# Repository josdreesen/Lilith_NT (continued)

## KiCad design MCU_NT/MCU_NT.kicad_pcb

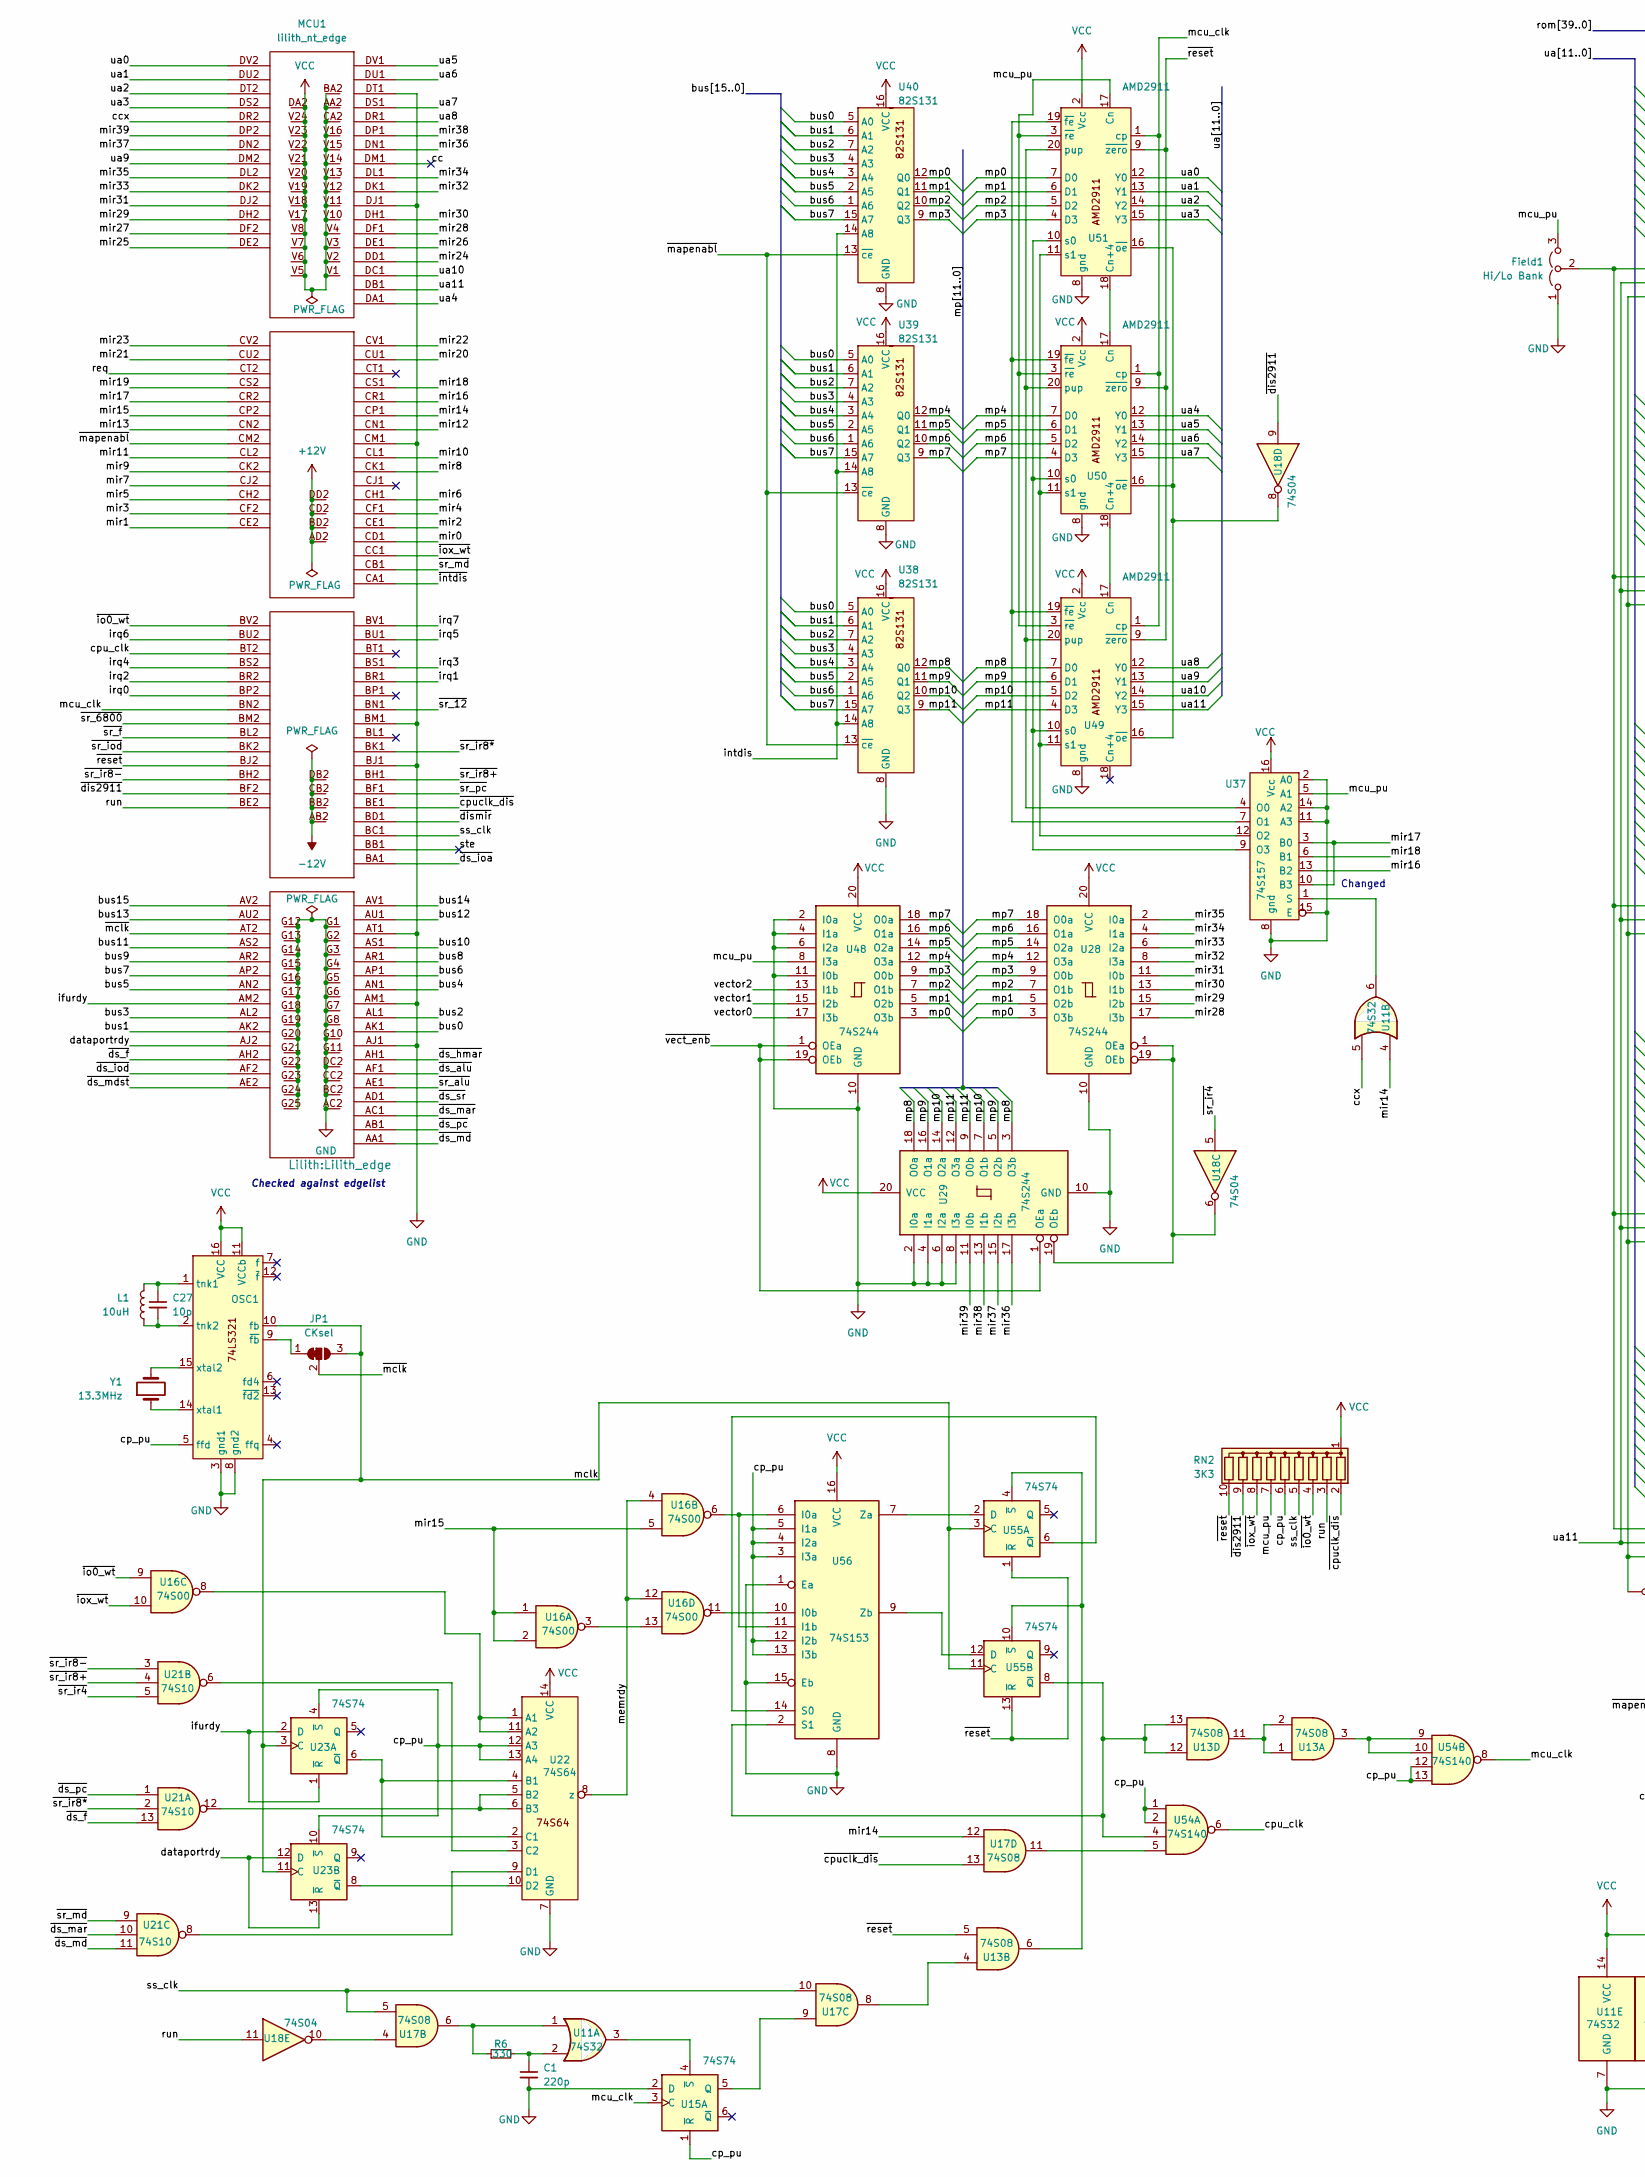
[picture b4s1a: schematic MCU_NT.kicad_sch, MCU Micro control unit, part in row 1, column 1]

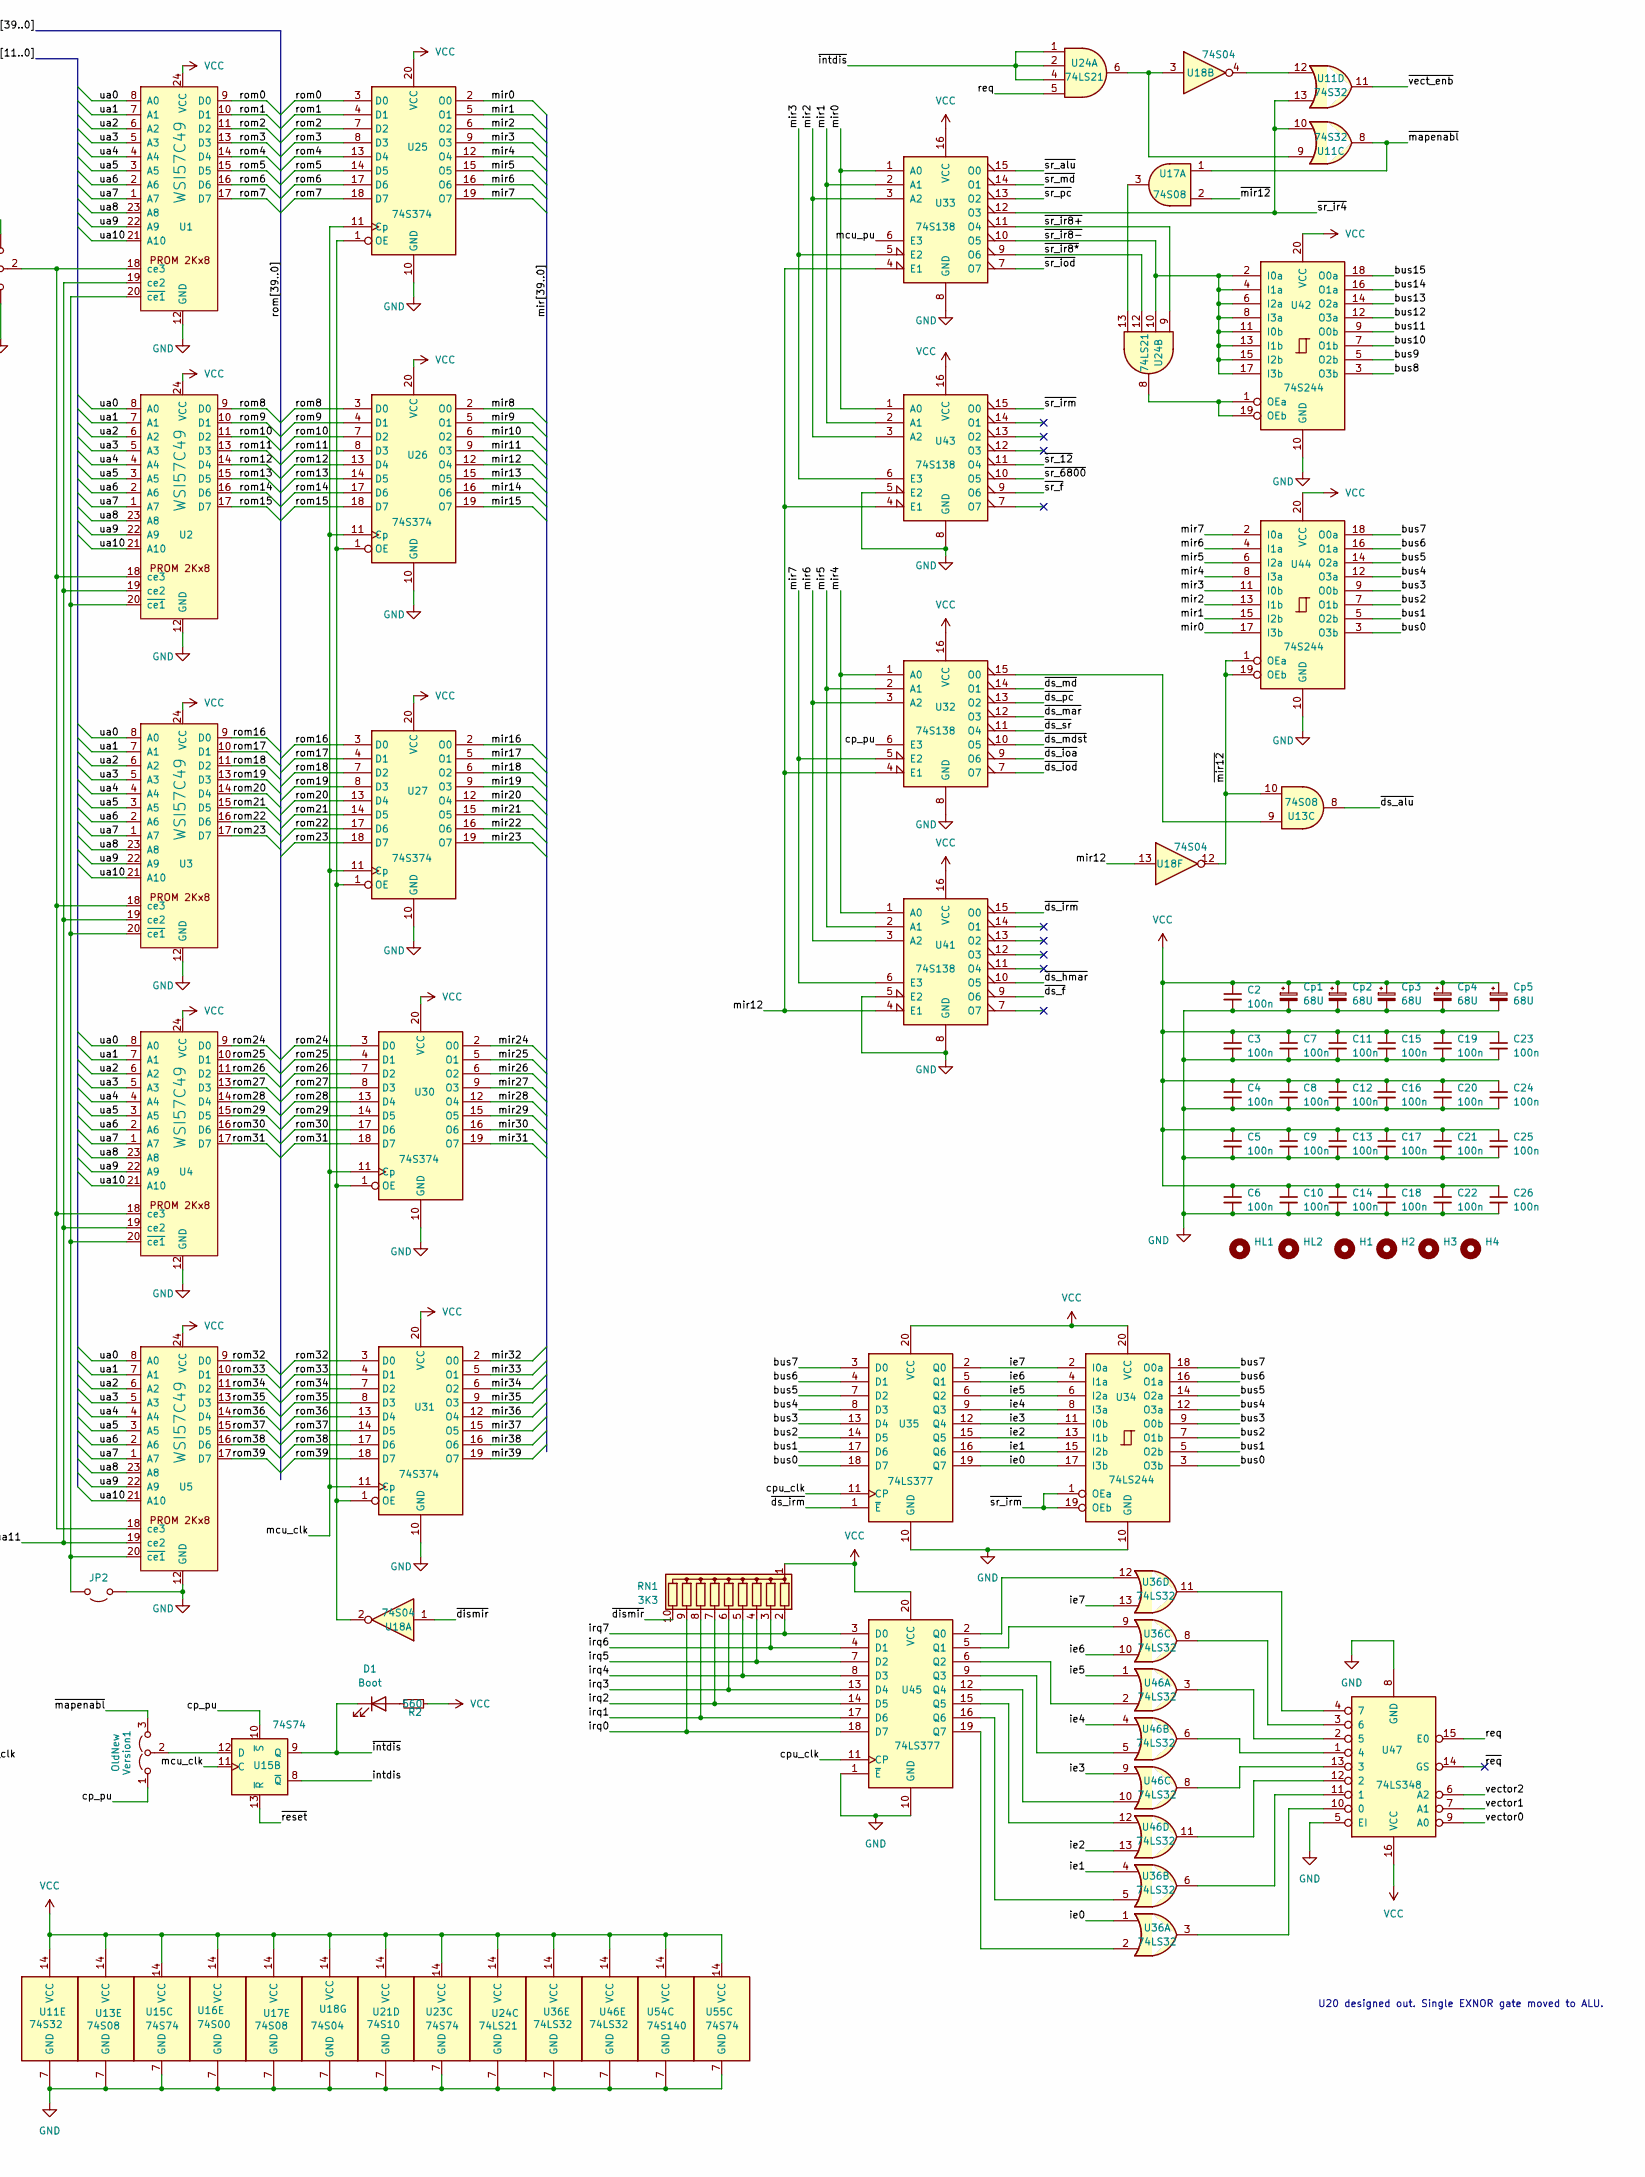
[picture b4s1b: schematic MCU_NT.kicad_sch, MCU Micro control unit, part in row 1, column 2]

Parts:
C1: 220p; C_Disc_D5.0mm_W2.5mm_P2.50mm
C2, C3, C4, C5, C6, C7, C8, C9, C10, C11, C12, C13, C14, C15, C16, C17, C18, C19, C20, C21, C22, C23, C24, C25, C26: 100n; C_1206_3216Metric_Pad1.33x1.80mm_HandSolder
C27: 10p; C_Disc_D5.0mm_W2.5mm_P2.50mm
Cp1, Cp2, Cp3, Cp4, Cp5: 68U; CP_PHP
D1: Boot; LED_D3.0mm_Horizontal_O3.81mm_Z10.0mm
Field1: Hi/Lo Bank; PinHeader_1x03_P2.54mm_Vertical
H1, H2, H3, H4: MountingHole; MountingHole_2.7mm
HL1, HL2: MountingHole; Handle
JP1: CKsel; SolderJumper-3_P1.3mm_Bridged12_RoundedPad1.0x1.5mm_NumberL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
JP2: Jumper_2_Open; SolderJumper-2_P1.3mm_Bridged_RoundedPad1.0x1.5mm
L1: 10uH; L_Axial_L5.3mm_D2.2mm_P7.62mm_Horizontal_Vishay_IM-1
MCU1: lilith_nt_edge; Lilith_edge
OSC1: 74LS321; DIP-16_W7.62mm
R2: 560; R_Axial_DIN0204_L3.6mm_D1.6mm_P7.62mm_Horizontal
R6: 330; R_Axial_DIN0204_L3.6mm_D1.6mm_P7.62mm_Horizontal
RN1, RN2: 3K3; R_Array_SIP10
U1, U2, U3, U4, U5: WSI57C49; DuoDil24
U11: 74S32; DIP-14_W7.62mm
U13, U17: 74S08; DIP-14_W7.62mm
U15, U23, U55: 74S74; DIP-14_W7.62mm
U16: 74S00; DIP-14_W7.62mm
U18: 74S04; DIP-14_W7.62mm
U21: 74S10; DIP-14_W7.62mm
U22: 74S64; DIP-14_W7.62mm
U24: 74LS21; DIP-14_W7.62mm
U25, U26, U27, U30, U31: 74S374; DIP-20_W7.62mm
U28, U29, U42, U44, U48: 74S244; DIP-20_W7.62mm
U32, U33, U41, U43: 74S138; DIP-16_W7.62mm
U34: 74LS244; DIP-20_W7.62mm
U35, U45: 74LS377; DIP-20_W7.62mm
U36, U46: 74LS32; DIP-14_W7.62mm
U37: 74S157; DIP-16_W7.62mm
U38, U39, U40: 82S131; DIP-16_W7.62mm_Socket
U47: 74LS348; DIP-16_W7.62mm
U49, U50, U51: AMD2911; DIP-20_W7.62mm
U54: 74S140; DIP-14_W7.62mm
U56: 74S153; DIP-16_W7.62mm
Version1: OldNew; PinHeader_1x03_P2.00mm_Vertical
Y1: 13.3MHz; Crystal_HC18-U_Horizontal

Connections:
+12V: MCU1.AD2, MCU1.BD2, MCU1.CD2, MCU1.DD2
-12V: MCU1.AB2, MCU1.BB2, MCU1.CB2, MCU1.DB2
/bus0: MCU1.AK1, U34.3 (O3b), U35.18 (D7), U38.5 (A0), U39.5 (A0), U40.5 (A0), U44.3 (O3b)
/bus1: MCU1.AK2, U34.5 (O2b), U35.17 (D6), U38.6 (A1), U39.6 (A1), U40.6 (A1), U44.5 (O2b)
/bus2: MCU1.AL1, U34.7 (O1b), U35.14 (D5), U38.7 (A2), U39.7 (A2), U40.7 (A2), U44.7 (O1b)
/bus3: MCU1.AL2, U34.9 (O0b), U35.13 (D4), U38.4 (A3), U39.4 (A3), U40.4 (A3), U44.9 (O0b)
/bus4: MCU1.AN1, U34.12 (O3a), U35.8 (D3), U38.3 (A4), U39.3 (A4), U40.3 (A4), U44.12 (O3a)
/bus5: MCU1.AN2, U34.14 (O2a), U35.7 (D2), U38.2 (A5), U39.2 (A5), U40.2 (A5), U44.14 (O2a)
/bus6: MCU1.AP1, U34.16 (O1a), U35.4 (D1), U38.1 (A6), U39.1 (A6), U40.1 (A6), U44.16 (O1a)
/bus7: MCU1.AP2, U34.18 (O0a), U35.3 (D0), U38.15 (A7), U39.15 (A7), U40.15 (A7), U44.18 (O0a)
/bus8: MCU1.AR1, U42.3 (O3b)
/bus9: MCU1.AR2, U42.5 (O2b)
/bus10: MCU1.AS1, U42.7 (O1b)
/bus11: MCU1.AS2, U42.9 (O0b)
/bus12: MCU1.AU1, U42.12 (O3a)
/bus13: MCU1.AU2, U42.14 (O2a)
/bus14: MCU1.AV1, U42.16 (O1a)
/bus15: MCU1.AV2, U42.18 (O0a)
/cc: MCU1.DM1
/ccx: MCU1.DR2, U11.5
/cp_pu: OSC1.5 (ffd), RN2.6 (R5), U15.1 (~R), U15.10 (~S), U22.12 (A3), U22.13 (A4), U23.4 (~S), U23.10 (~S), U32.6 (E3), U54.1, U54.2, U54.12, U54.13, U56.3 (I3a), U56.4 (I2a), U56.5 (I1a), U56.12 (I2b), U56.13 (I3b), Version1.1 (A)
/cpu_clk: MCU1.BT2, U35.11 (CP), U45.11 (CP), U54.6
/dataportrdy: MCU1.AJ2, U23.12 (D), U23.13 (~R)
/ie0: U34.17 (I3b), U35.19 (Q7), U36.1
/ie1: U34.15 (I2b), U35.16 (Q6), U36.4
/ie2: U34.13 (I1b), U35.15 (Q5), U46.13
/ie3: U34.11 (I0b), U35.12 (Q4), U46.9
/ie4: U34.8 (I3a), U35.9 (Q3), U46.4
/ie5: U34.6 (I2a), U35.6 (Q2), U46.1
/ie6: U34.4 (I1a), U35.5 (Q1), U36.10
/ie7: U34.2 (I0a), U35.2 (Q0), U36.13
/ifurdy: MCU1.AM2, U23.1 (~R), U23.2 (D)
/intdis: U15.8 (~Q), U38.14 (A8), U39.14 (A8), U40.14 (A8)
/irq0: MCU1.BP2, RN1.9 (R8), U45.18 (D7)
/irq1: MCU1.BR1, RN1.8 (R7), U45.17 (D6)
/irq2: MCU1.BR2, RN1.7 (R6), U45.14 (D5)
/irq3: MCU1.BS1, RN1.6 (R5), U45.13 (D4)
/irq4: MCU1.BS2, RN1.5 (R4), U45.8 (D3)
/irq5: MCU1.BU1, RN1.4 (R3), U45.7 (D2)
/irq6: MCU1.BU2, RN1.3 (R2), U45.4 (D1)
/irq7: MCU1.BV1, RN1.2 (R1), U45.3 (D0)
/mclk: JP1.3 (B), OSC1.10 (fb), U23.3 (C), U23.11 (C), U55.3 (C), U55.11 (C)
/mcu_clk: MCU1.BN2, U15.3 (C), U15.11 (C), U25.11 (Cp), U26.11 (Cp), U27.11 (Cp), U30.11 (Cp), U31.11 (Cp), U49.1 (cp), U50.1 (cp), U51.1 (cp), U54.8
/mcu_pu: Field1.3 (B), RN2.7 (R6), U33.6 (E3), U37.5 (A1), U48.8 (I3a), U49.3 (~re), U50.3 (~re), U51.3 (~re), U51.17 (Cn)
/memrdy: U16.4, U16.12, U22.8 (z)
/mir0: MCU1.CD1, U25.2 (O0), U33.1 (A0), U43.1 (A0), U44.17 (I3b)
/mir1: MCU1.CE2, U25.5 (O1), U33.2 (A1), U43.2 (A1), U44.15 (I2b)
/mir2: MCU1.CE1, U25.6 (O2), U33.3 (A2), U43.3 (A2), U44.13 (I1b)
/mir3: MCU1.CF2, U25.9 (O3), U33.5 (E2), U43.6 (E3), U44.11 (I0b)
/mir4: MCU1.CF1, U25.12 (O4), U32.1 (A0), U41.1 (A0), U44.8 (I3a)
/mir5: MCU1.CH2, U25.15 (O5), U32.2 (A1), U41.2 (A1), U44.6 (I2a)
/mir6: MCU1.CH1, U25.16 (O6), U32.3 (A2), U41.3 (A2), U44.4 (I1a)
/mir7: MCU1.CJ2, U25.19 (O7), U32.5 (E2), U41.6 (E3), U44.2 (I0a)
/mir8: MCU1.CK1, U26.2 (O0)
/mir9: MCU1.CK2, U26.5 (O1)
/mir10: MCU1.CL1, U26.6 (O2)
/mir11: MCU1.CL2, U26.9 (O3)
/mir12: MCU1.CN1, U18.13, U26.12 (O4), U32.4 (E1), U33.4 (E1), U41.4 (E1), U43.4 (E1)
/mir13: MCU1.CN2, U26.15 (O5)
/mir14: MCU1.CP1, U11.4, U17.12, U26.16 (O6)
/mir15: MCU1.CP2, U16.1, U16.2, U16.5, U26.19 (O7)
/mir16: MCU1.CR1, U27.2 (O0), U37.13 (B2)
/mir17: MCU1.CR2, U27.5 (O1), U37.3 (B0), U37.10 (B3)
/mir18: MCU1.CS1, U27.6 (O2), U37.6 (B1)
/mir19: MCU1.CS2, U27.9 (O3)
/mir20: MCU1.CU1, U27.12 (O4)
/mir21: MCU1.CU2, U27.15 (O5)
/mir22: MCU1.CV1, U27.16 (O6)
/mir23: MCU1.CV2, U27.19 (O7)
/mir24: MCU1.DD1, U30.2 (O0)
/mir25: MCU1.DE2, U30.5 (O1)
/mir26: MCU1.DE1, U30.6 (O2)
/mir27: MCU1.DF2, U30.9 (O3)
/mir28: MCU1.DF1, U28.17 (I3b), U30.12 (O4)
/mir29: MCU1.DH2, U28.15 (I2b), U30.15 (O5)
/mir30: MCU1.DH1, U28.13 (I1b), U30.16 (O6)
/mir31: MCU1.DJ2, U28.11 (I0b), U30.19 (O7)
/mir32: MCU1.DK1, U28.8 (I3a), U31.2 (O0)
/mir33: MCU1.DK2, U28.6 (I2a), U31.5 (O1)
/mir34: MCU1.DL1, U28.4 (I1a), U31.6 (O2)
/mir35: MCU1.DL2, U28.2 (I0a), U31.9 (O3)
/mir36: MCU1.DN1, U29.17 (I3b), U31.12 (O4)
/mir37: MCU1.DN2, U29.15 (I2b), U31.15 (O5)
/mir38: MCU1.DP1, U29.13 (I1b), U31.16 (O6)
/mir39: MCU1.DP2, U29.11 (I0b), U31.19 (O7)
/mp0: U28.3 (O3b), U40.12 (Q0), U48.3 (O3b), U51.7 (D0)
/mp1: U28.5 (O2b), U40.11 (Q1), U48.5 (O2b), U51.6 (D1)
/mp2: U28.7 (O1b), U40.10 (Q2), U48.7 (O1b), U51.5 (D2)
/mp3: U28.9 (O0b), U40.9 (Q3), U48.9 (O0b), U51.4 (D3)
/mp4: U28.12 (O3a), U39.12 (Q0), U48.12 (O3a), U50.7 (D0)
/mp5: U28.14 (O2a), U39.11 (Q1), U48.14 (O2a), U50.6 (D1)
/mp6: U28.16 (O1a), U39.10 (Q2), U48.16 (O1a), U50.5 (D2)
/mp7: U28.18 (O0a), U39.9 (Q3), U48.18 (O0a), U50.4 (D3)
/mp8: U29.3 (O3b), U29.18 (O0a), U38.12 (Q0), U49.7 (D0)
/mp9: U29.5 (O2b), U29.16 (O1a), U38.11 (Q1), U49.6 (D1)
/mp10: U29.7 (O1b), U29.14 (O2a), U38.10 (Q2), U49.5 (D2)
/mp11: U29.9 (O0b), U29.12 (O3a), U38.9 (Q3), U49.4 (D3)
/req: MCU1.CT2, U24.5, U47.15 (E0)
/rom0: U1.9 (D0), U25.3 (D0)
/rom1: U1.10 (D1), U25.4 (D1)
/rom2: U1.11 (D2), U25.7 (D2)
/rom3: U1.13 (D3), U25.8 (D3)
/rom4: U1.14 (D4), U25.13 (D4)
/rom5: U1.15 (D5), U25.14 (D5)
/rom6: U1.16 (D6), U25.17 (D6)
/rom7: U1.17 (D7), U25.18 (D7)
/rom8: U2.9 (D0), U26.3 (D0)
/rom9: U2.10 (D1), U26.4 (D1)
/rom10: U2.11 (D2), U26.7 (D2)
/rom11: U2.13 (D3), U26.8 (D3)
/rom12: U2.14 (D4), U26.13 (D4)
/rom13: U2.15 (D5), U26.14 (D5)
/rom14: U2.16 (D6), U26.17 (D6)
/rom15: U2.17 (D7), U26.18 (D7)
/rom16: U3.9 (D0), U27.3 (D0)
/rom17: U3.10 (D1), U27.4 (D1)
/rom18: U3.11 (D2), U27.7 (D2)
/rom19: U3.13 (D3), U27.8 (D3)
/rom20: U3.14 (D4), U27.13 (D4)
/rom21: U3.15 (D5), U27.14 (D5)
/rom22: U3.16 (D6), U27.17 (D6)
/rom23: U3.17 (D7), U27.18 (D7)
/rom24: U4.9 (D0), U30.3 (D0)
/rom25: U4.10 (D1), U30.4 (D1)
/rom26: U4.11 (D2), U30.7 (D2)
/rom27: U4.13 (D3), U30.8 (D3)
/rom28: U4.14 (D4), U30.13 (D4)
/rom29: U4.15 (D5), U30.14 (D5)
/rom30: U4.16 (D6), U30.17 (D6)
/rom31: U4.17 (D7), U30.18 (D7)
/rom32: U5.9 (D0), U31.3 (D0)
/rom33: U5.10 (D1), U31.4 (D1)
/rom34: U5.11 (D2), U31.7 (D2)
/rom35: U5.13 (D3), U31.8 (D3)
/rom36: U5.14 (D4), U31.13 (D4)
/rom37: U5.15 (D5), U31.14 (D5)
/rom38: U5.16 (D6), U31.17 (D6)
/rom39: U5.17 (D7), U31.18 (D7)
/run: MCU1.BE2, RN2.3 (R2), U18.11
/ss_clk: MCU1.BC1, RN2.5 (R4), U17.5, U17.10
/ste: MCU1.BB1
/ua0: MCU1.DV2, U1.8 (A0), U2.8 (A0), U3.8 (A0), U4.8 (A0), U5.8 (A0), U51.12 (Y0)
/ua1: MCU1.DU2, U1.7 (A1), U2.7 (A1), U3.7 (A1), U4.7 (A1), U5.7 (A1), U51.13 (Y1)
/ua2: MCU1.DT2, U1.6 (A2), U2.6 (A2), U3.6 (A2), U4.6 (A2), U5.6 (A2), U51.14 (Y2)
/ua3: MCU1.DS2, U1.5 (A3), U2.5 (A3), U3.5 (A3), U4.5 (A3), U5.5 (A3), U51.15 (Y3)
/ua4: MCU1.DA1, U1.4 (A4), U2.4 (A4), U3.4 (A4), U4.4 (A4), U5.4 (A4), U50.12 (Y0)
/ua5: MCU1.DV1, U1.3 (A5), U2.3 (A5), U3.3 (A5), U4.3 (A5), U5.3 (A5), U50.13 (Y1)
/ua6: MCU1.DU1, U1.2 (A6), U2.2 (A6), U3.2 (A6), U4.2 (A6), U5.2 (A6), U50.14 (Y2)
/ua7: MCU1.DS1, U1.1 (A7), U2.1 (A7), U3.1 (A7), U4.1 (A7), U5.1 (A7), U50.15 (Y3)
/ua8: MCU1.DR1, U1.23 (A8), U2.23 (A8), U3.23 (A8), U4.23 (A8), U5.23 (A8), U49.12 (Y0)
/ua9: MCU1.DM2, U1.22 (A9), U2.22 (A9), U3.22 (A9), U4.22 (A9), U5.22 (A9), U49.13 (Y1)
/ua10: MCU1.DC1, U1.21 (A10), U2.21 (A10), U3.21 (A10), U4.21 (A10), U5.21 (A10), U49.14 (Y2)
/ua11: MCU1.DB1, U1.19 (ce2), U2.19 (ce2), U3.19 (ce2), U4.19 (ce2), U5.19 (ce2), U49.15 (Y3)
/vector0: U47.9 (A0), U48.17 (I3b)
/vector1: U47.7 (A1), U48.15 (I2b)
/vector2: U47.6 (A2), U48.13 (I1b)
/~cpuclk_dis: MCU1.BE1, RN2.2 (R1), U17.13
/~dis2911: MCU1.BF2, RN2.9 (R8), U18.9
/~dismir: MCU1.BD1, RN1.10 (R9), U18.1
/~ds_alu: MCU1.AF1, U13.8
/~ds_f: MCU1.AH2, U21.13, U41.9 (O6)
/~ds_hmar: MCU1.AH1, U41.10 (O5)
/~ds_ioa: MCU1.BA1, U32.9 (O6)
/~ds_iod: MCU1.AF2, U32.7 (O7)
/~ds_irm: U35.1 (~E), U41.15 (O0)
/~ds_mar: MCU1.AC1, U21.10, U32.12 (O3)
/~ds_mdst: MCU1.AE2, U32.10 (O5)
/~ds_md: MCU1.AA1, U21.11, U32.14 (O1)
/~ds_pc: MCU1.AB1, U21.1, U32.13 (O2)
/~ds_sr: MCU1.AD1, U32.11 (O4)
/~intdis: D1.1 (K), MCU1.CA1, U15.9 (Q), U24.1, U24.2, U24.4
/~io0_wait: MCU1.BV2, RN2.4 (R3), U16.9
/~iox_wait: MCU1.CC1, RN2.8 (R7), U16.10
/~mapenabl: MCU1.CM2, U11.8, U17.1, U38.13 (~ce), U39.13 (~ce), U40.13 (~ce), Version1.3 (B)
/~mclk: JP1.2 (C), MCU1.AT2
/~mir12: U13.10, U17.2, U18.12, U44.1 (OEa), U44.19 (OEb)
/~req: U47.14 (GS)
/~reset: MCU1.BJ2, RN2.10 (R9), U13.5, U15.13 (~R), U49.9 (~zero), U50.9 (~zero), U51.9 (~zero), U55.1 (~R), U55.13 (~R)
/~sr_12: MCU1.BN1, U43.11 (O4)
/~sr_6800: MCU1.BM2, U43.10 (O5)
/~sr_alu: MCU1.AE1, U33.15 (O0)
/~sr_f: MCU1.BL2, U43.9 (O6)
/~sr_iod: MCU1.BK2, U33.7 (O7)
/~sr_ir4: U11.10, U11.13, U18.5, U21.5, U33.12 (O3)
/~sr_ir8*: MCU1.BK1, U21.2, U24.12, U33.9 (O6)
/~sr_ir8+: MCU1.BH1, U21.4, U24.9, U33.11 (O4)
/~sr_ir8-: MCU1.BH2, U21.3, U24.10, U33.10 (O5), U42.2 (I0a), U42.4 (I1a), U42.6 (I2a), U42.8 (I3a), U42.11 (I0b), U42.13 (I1b), U42.15 (I2b), U42.17 (I3b)
/~sr_irm: U34.1 (OEa), U34.19 (OEb), U43.15 (O0)
/~sr_md: MCU1.CB1, U21.9, U33.14 (O1)
/~sr_pc: MCU1.BF1, U33.13 (O2)
/~vect_enb: U11.11, U29.1 (OEa), U48.1 (OEa), U48.19 (OEb)
GND: C1.2, C2.2, C3.2, C4.2, C5.2, C6.2, C7.2, C8.2, C9.2, C10.2, C11.2, C12.2, C13.2, C14.2, C15.2, C16.2, C17.2, C18.2, C19.2, C20.2, C21.2, C22.2, C23.2, C24.2, C25.2, C26.2, Cp1.2, Cp2.2, Cp3.2, Cp4.2, Cp5.2, Field1.1 (A), JP2.1 (A), MCU1.AC2, MCU1.AJ1, MCU1.AM1, MCU1.AT1, MCU1.BC2, MCU1.BJ1, MCU1.BM1, MCU1.CC2, MCU1.CM1, MCU1.DC2, MCU1.DJ1, MCU1.DT1, MCU1.G1 (GND), MCU1.G2 (GND), MCU1.G3 (GND), MCU1.G4 (GND), MCU1.G5 (GND), MCU1.G6 (GND), MCU1.G7 (GND), MCU1.G8 (GND), MCU1.G10, MCU1.G11, MCU1.G12, MCU1.G13, MCU1.G14, MCU1.G15, MCU1.G16, MCU1.G17, MCU1.G18, MCU1.G19, MCU1.G20, MCU1.G21, MCU1.G22, MCU1.G23, MCU1.G24, MCU1.G25, OSC1.3 (gnd1), OSC1.8 (gnd2), U1.12 (GND), U2.12 (GND), U3.12 (GND), U4.12 (GND), U5.12 (GND), U11.7 (GND), U13.7 (GND), U15.2 (D), U15.7 (GND), U16.7 (GND), U17.7 (GND), U18.7 (GND), U21.7 (GND), U22.7 (GND), U23.7 (GND), U24.7 (GND), U25.10 (GND), U26.10 (GND), U27.10 (GND), U28.10 (GND), U29.2 (I0a), U29.4 (I1a), U29.6 (I2a), U29.8 (I3a), U29.10 (GND), U30.10 (GND), U31.10 (GND), U32.8 (GND), U33.8 (GND), U34.10 (GND), U35.10 (GND), U36.7 (GND), U37.2 (A0), U37.8 (gnd), U37.11 (A3), U37.14 (A2), U37.15 (E), U38.8 (GND), U39.8 (GND), U40.8 (GND), U41.5 (E2), U41.8 (GND), U42.10 (GND), U43.5 (E2), U43.8 (GND), U44.10 (GND), U45.1 (~E), U45.10 (GND), U46.7 (GND), U47.5 (EI), U47.8 (GND), U48.2 (I0a), U48.4 (I1a), U48.6 (I2a), U48.10 (GND), U48.11 (I0b), U49.8 (gnd), U50.8 (gnd), U51.8 (gnd), U54.7 (GND), U55.7 (GND), U56.1 (Ea), U56.8 (GND), U56.15 (Eb)
unnamed: C1.1, R6.2, U11.2
unnamed: D1.2 (A), R2.2
unnamed: Field1.2 (C), U1.18 (ce3), U2.18 (ce3), U3.18 (ce3), U4.18 (ce3), U5.18 (ce3)
unnamed: JP1.1 (A), OSC1.9 (~fb)
unnamed: JP2.2 (B), U1.20 (~ce1), U2.20 (~ce1), U3.20 (~ce1), U4.20 (~ce1), U5.20 (~ce1)
unnamed: C27.1, L1.1, OSC1.1 (tnk1)
unnamed: C27.2, L1.2, OSC1.2 (tnk2)
unnamed: OSC1.14 (xtal1), Y1.1
unnamed: OSC1.15 (xtal2), Y1.2
unnamed: R6.1, U11.1, U17.6
unnamed: U11.9, U18.3, U24.6
unnamed: U11.12, U18.4
unnamed: U13.1, U13.2, U13.11
unnamed: U13.3, U54.9, U54.10
unnamed: U13.4, U17.8
unnamed: U15.5 (Q), U17.9
unnamed: U11.3, U15.4 (~S)
unnamed: U15.12 (D), Version1.2 (C)
unnamed: U16.3, U16.13
unnamed: U17.3, U24.13
unnamed: U17.4, U18.10
unnamed: U17.11, U54.5
unnamed: U16.8, U22.1 (A1), U22.11 (A2)
unnamed: U22.2 (C1), U22.4 (B1), U23.6 (~Q)
unnamed: U21.12, U22.5 (B2), U22.6 (B3)
unnamed: U21.6, U22.3 (C2)
unnamed: U21.8, U22.9 (D1)
unnamed: U22.10 (D2), U23.8 (~Q)
unnamed: U18.2, U25.1 (OE), U26.1 (OE), U27.1 (OE), U30.1 (OE), U31.1 (OE)
unnamed: U18.6, U28.1 (OEa), U28.19 (OEb), U29.19 (OEb)
unnamed: U13.9, U32.15 (O0)
unnamed: U37.4 (O0), U49.20 (pup), U50.20 (pup), U51.20 (pup)
unnamed: U37.7 (O1), U49.19 (~fe), U50.19 (~fe), U51.19 (~fe)
unnamed: U37.12 (O2), U49.11 (s1), U50.11 (s1), U51.11 (s1)
unnamed: U37.9 (O3), U49.10 (s0), U50.10 (s0), U51.10 (s0)
unnamed: U11.6, U37.1 (S)
unnamed: U24.8, U42.1 (OEa), U42.19 (OEb)
unnamed: U36.12, U45.2 (Q0)
unnamed: U36.9, U45.5 (Q1)
unnamed: U45.6 (Q2), U46.2
unnamed: U45.9 (Q3), U46.5
unnamed: U45.12 (Q4), U46.10
unnamed: U45.15 (Q5), U46.12
unnamed: U36.5, U45.16 (Q6)
unnamed: U36.2, U45.19 (Q7)
unnamed: U36.3, U47.10 (0)
unnamed: U36.6, U47.11 (1)
unnamed: U46.11, U47.12 (2)
unnamed: U46.8, U47.13 (3)
unnamed: U46.6, U47.1 (4)
unnamed: U46.3, U47.2 (5)
unnamed: U36.8, U47.3 (6)
unnamed: U36.11, U47.4 (7)
unnamed: U49.17 (Cn), U50.18 (Cn+4)
unnamed: U18.8, U49.16 (~oe), U50.16 (~oe), U51.16 (~oe)
unnamed: U50.17 (Cn), U51.18 (Cn+4)
unnamed: U55.2 (D), U56.7 (Za)
unnamed: U55.6 (~Q), U56.14 (S0)
unnamed: U13.6, U55.4 (~S), U55.10 (~S)
unnamed: U55.12 (D), U56.9 (Zb)
unnamed: U13.12, U13.13, U54.4, U55.8 (~Q), U56.2 (S1)
unnamed: U16.6, U56.6 (I0a), U56.11 (I1b)
unnamed: U16.11, U56.10 (I0b)
VCC: C2.1, C3.1, C4.1, C5.1, C6.1, C7.1, C8.1, C9.1, C10.1, C11.1, C12.1, C13.1, C14.1, C15.1, C16.1, C17.1, C18.1, C19.1, C20.1, C21.1, C22.1, C23.1, C24.1, C25.1, C26.1, Cp1.1, Cp2.1, Cp3.1, Cp4.1, Cp5.1, MCU1.AA2, MCU1.BA2, MCU1.CA2, MCU1.DA2, MCU1.V1 (VCC), MCU1.V2 (VCC), MCU1.V3 (VCC), MCU1.V4 (VCC), MCU1.V5 (VCC), MCU1.V6 (VCC), MCU1.V7 (VCC), MCU1.V8 (VCC), MCU1.V10, MCU1.V11, MCU1.V12, MCU1.V13, MCU1.V14, MCU1.V15, MCU1.V16, MCU1.V17, MCU1.V18, MCU1.V19, MCU1.V20, MCU1.V21, MCU1.V22, MCU1.V23, MCU1.V24, OSC1.11 (VCCb), OSC1.16 (VCC), R2.1, RN1.1 (common), RN2.1 (common), U1.24 (VCC), U2.24 (VCC), U3.24 (VCC), U4.24 (VCC), U5.24 (VCC), U11.14 (VCC), U13.14 (VCC), U15.14 (VCC), U16.14 (VCC), U17.14 (VCC), U18.14 (VCC), U21.14 (VCC), U22.14 (VCC), U23.14 (VCC), U24.14 (VCC), U25.20 (VCC), U26.20 (VCC), U27.20 (VCC), U28.20 (VCC), U29.20 (VCC), U30.20 (VCC), U31.20 (VCC), U32.16 (VCC), U33.16 (VCC), U34.20 (VCC), U35.20 (VCC), U36.14 (VCC), U37.16 (Vcc), U38.16 (VCC), U39.16 (VCC), U40.16 (VCC), U41.16 (VCC), U42.20 (VCC), U43.16 (VCC), U44.20 (VCC), U45.20 (VCC), U46.14 (VCC), U47.16 (VCC), U48.20 (VCC), U49.2 (Vcc), U50.2 (Vcc), U51.2 (Vcc), U54.14 (VCC), U55.14 (VCC), U56.16 (VCC)

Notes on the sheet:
Checked against edgelist
Changed
U20 designed out. Single EXNOR gate moved to ALU.

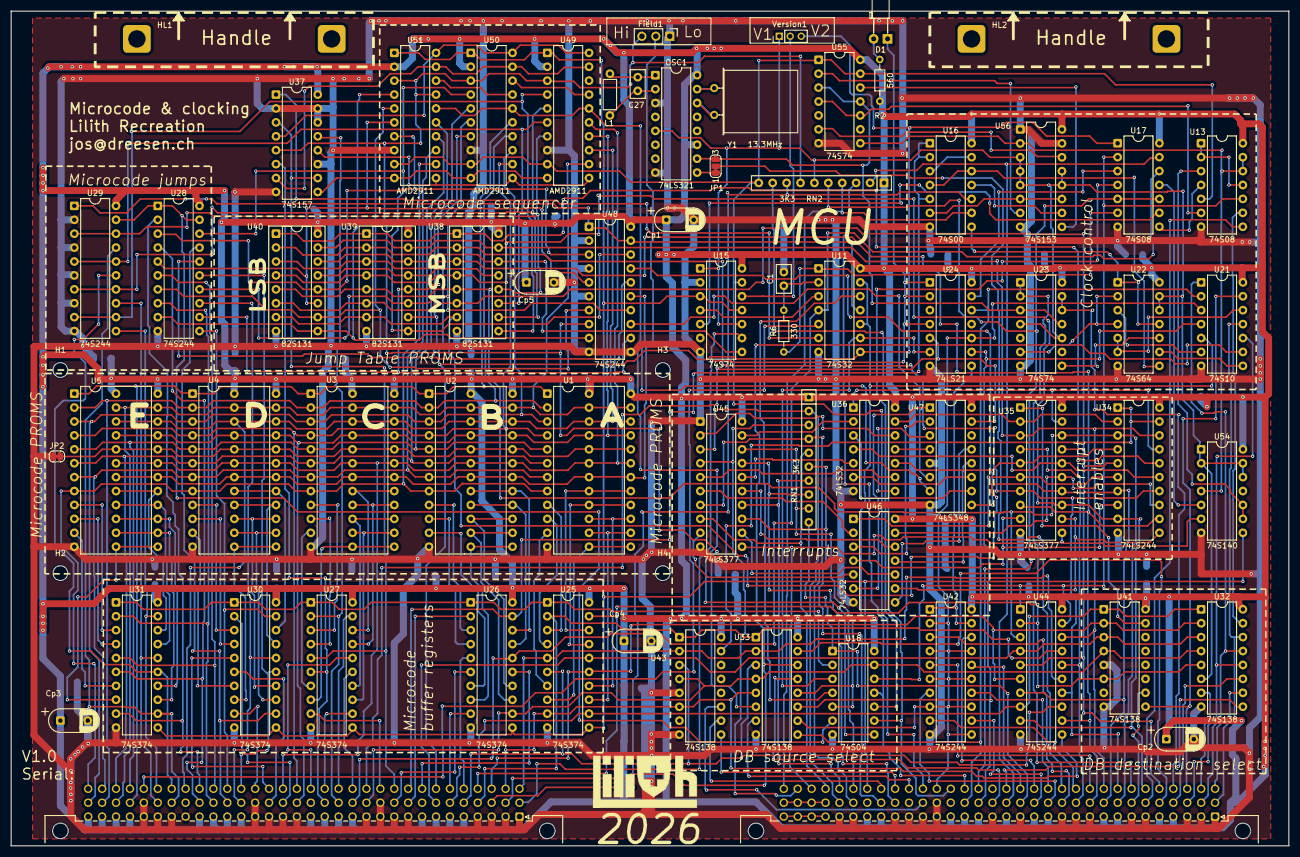
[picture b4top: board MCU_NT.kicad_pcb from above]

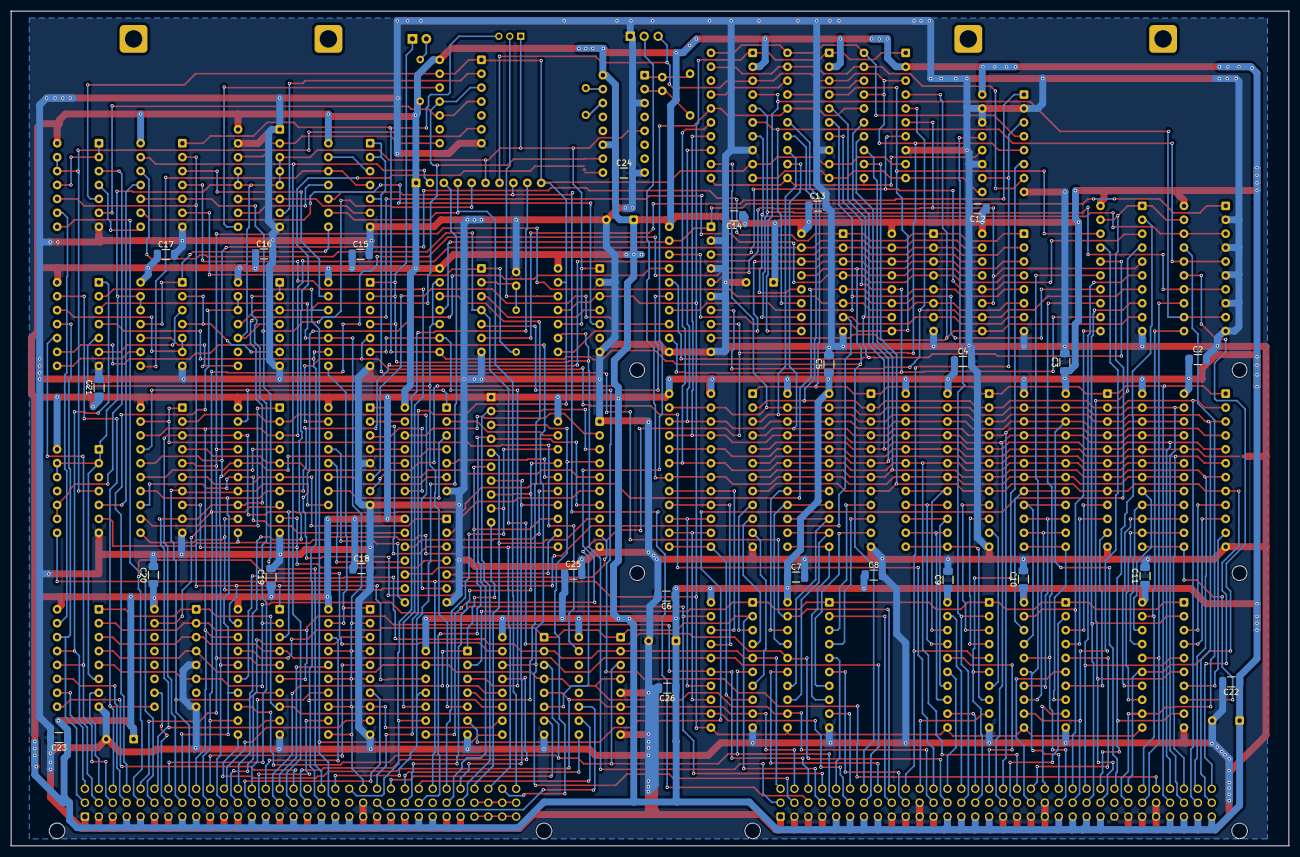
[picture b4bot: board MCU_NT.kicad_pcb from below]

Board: 2 copper layers, 233.3 x 152.4 mm, 96 parts (25 on the bottom side), 253 nets.
